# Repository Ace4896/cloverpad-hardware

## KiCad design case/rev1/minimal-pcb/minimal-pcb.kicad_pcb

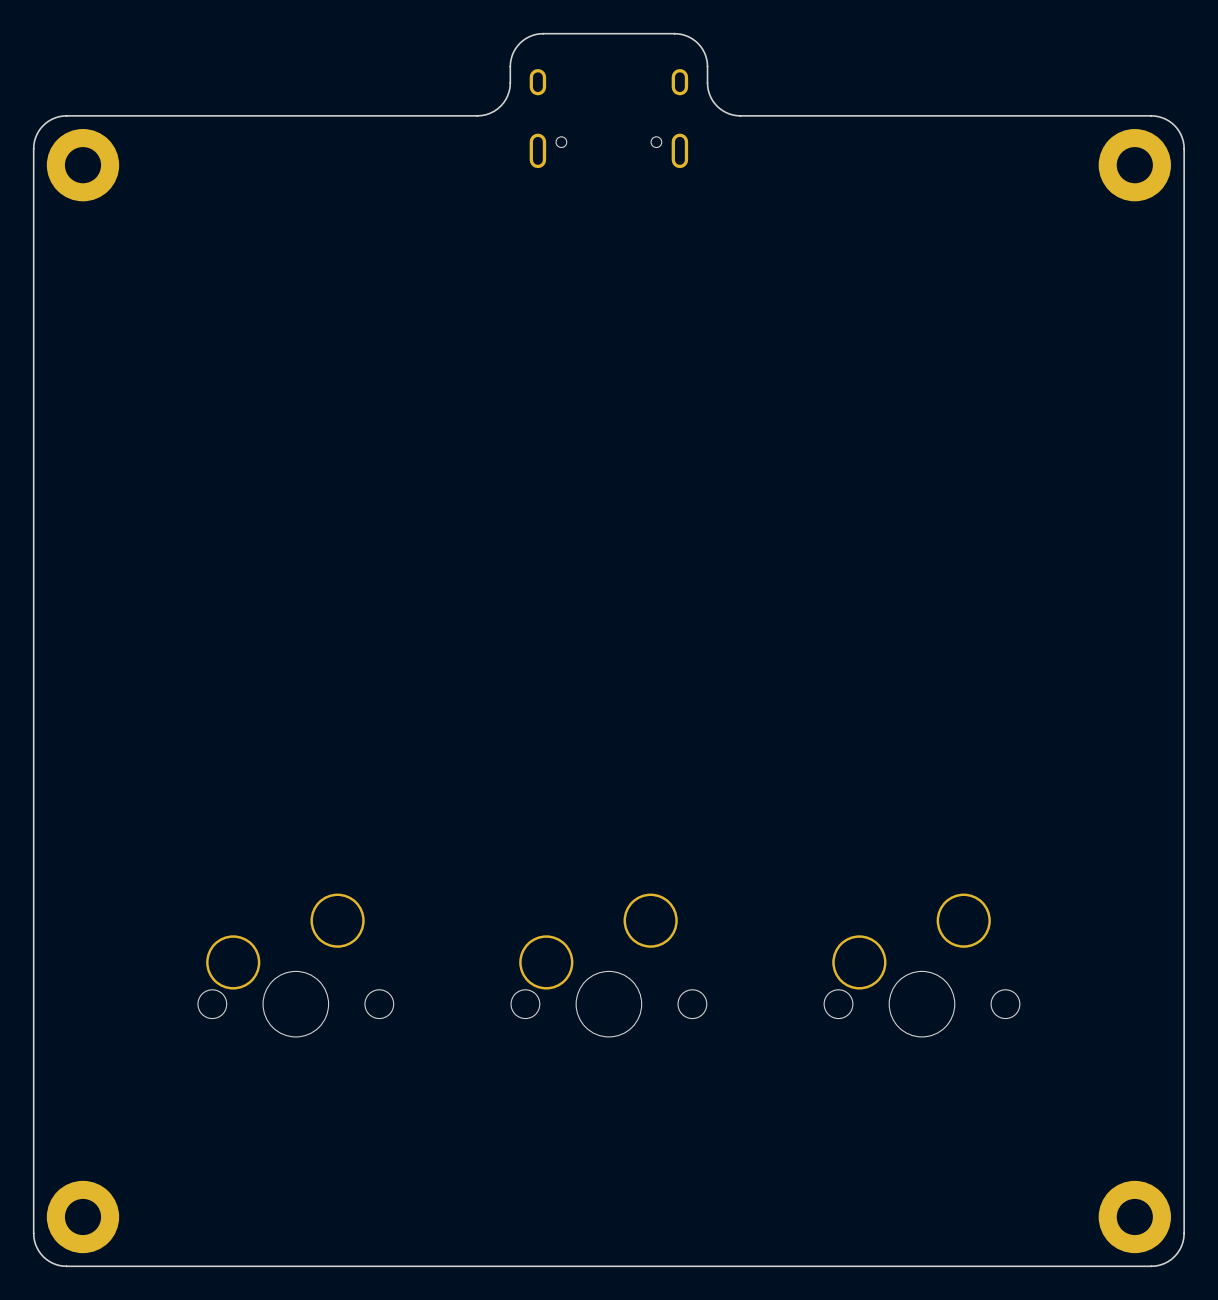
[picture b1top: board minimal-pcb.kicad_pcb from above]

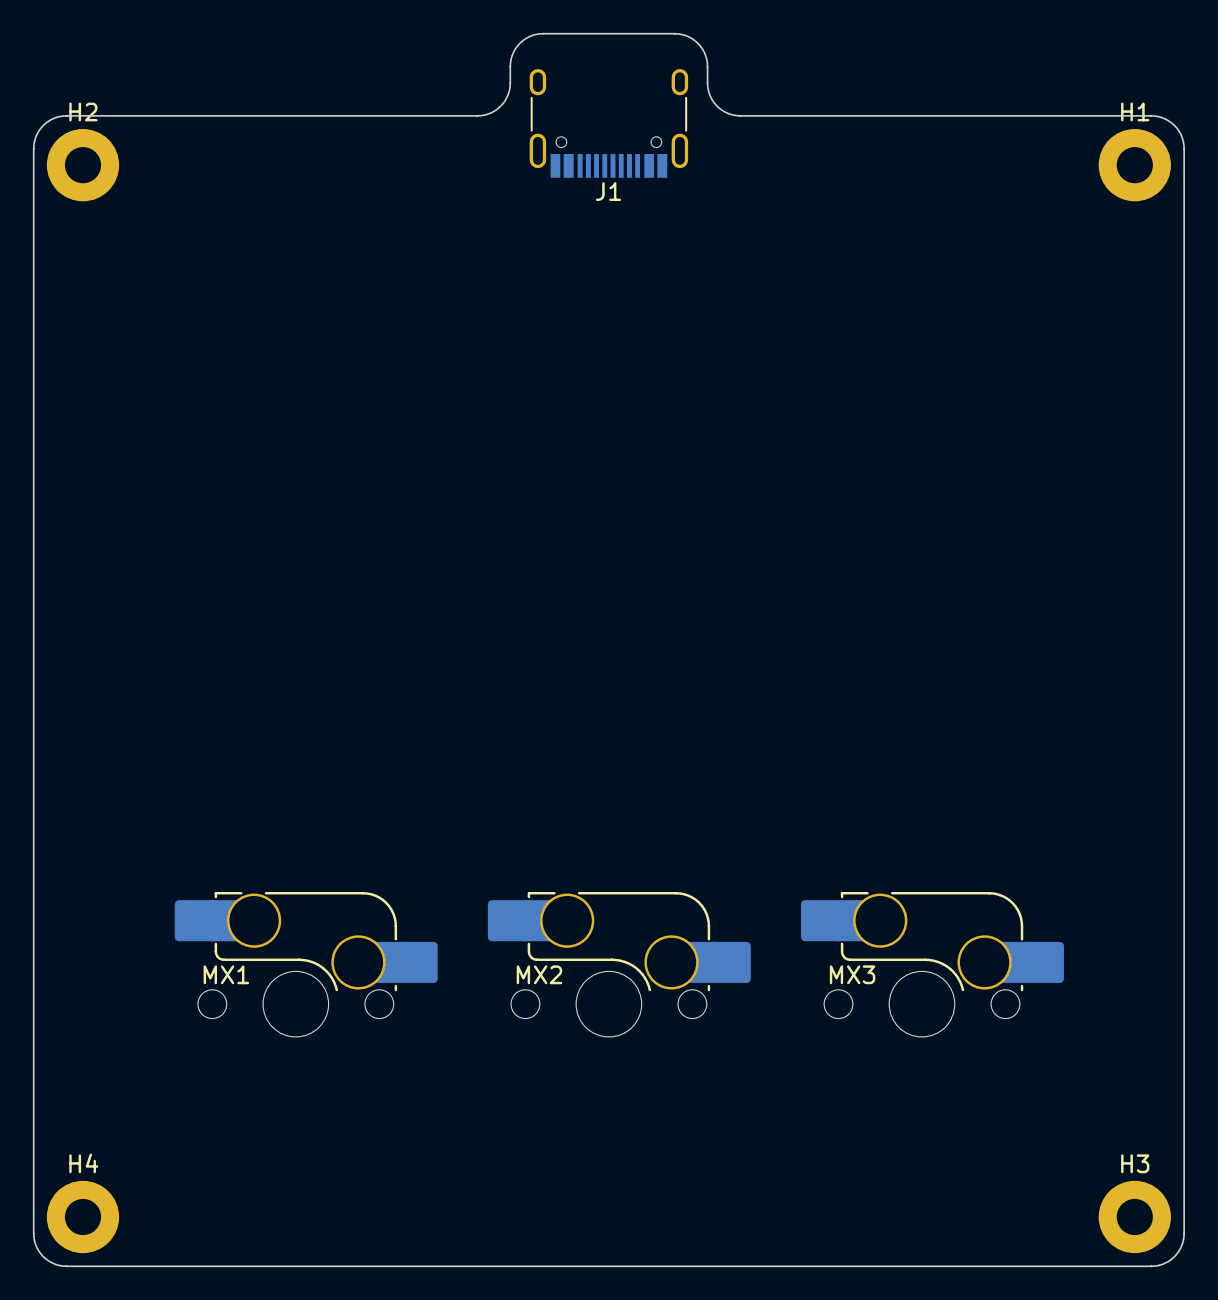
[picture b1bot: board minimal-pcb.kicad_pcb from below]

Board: 2 copper layers, 70.0 x 75.0 mm, 8 parts (8 on the bottom side), 2 nets, no tracks yet.

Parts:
H1, H2, H3, H4: Mounting Hole; MountingHole_2.2mm_M2_Pad
J1: USB_C_Receptacle_USB2.0; USB_C_Receptacle_HRO_TYPE-C-31-M-12
MX1, MX2, MX3: MX_SW_HS; SW_MX_HS_1u

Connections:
unnamed: J1.A1 (GND), J1.A12 (GND), J1.B1 (GND), J1.B12 (GND)
unnamed: J1.A4 (VBUS), J1.A9 (VBUS), J1.B4 (VBUS), J1.B9 (VBUS)

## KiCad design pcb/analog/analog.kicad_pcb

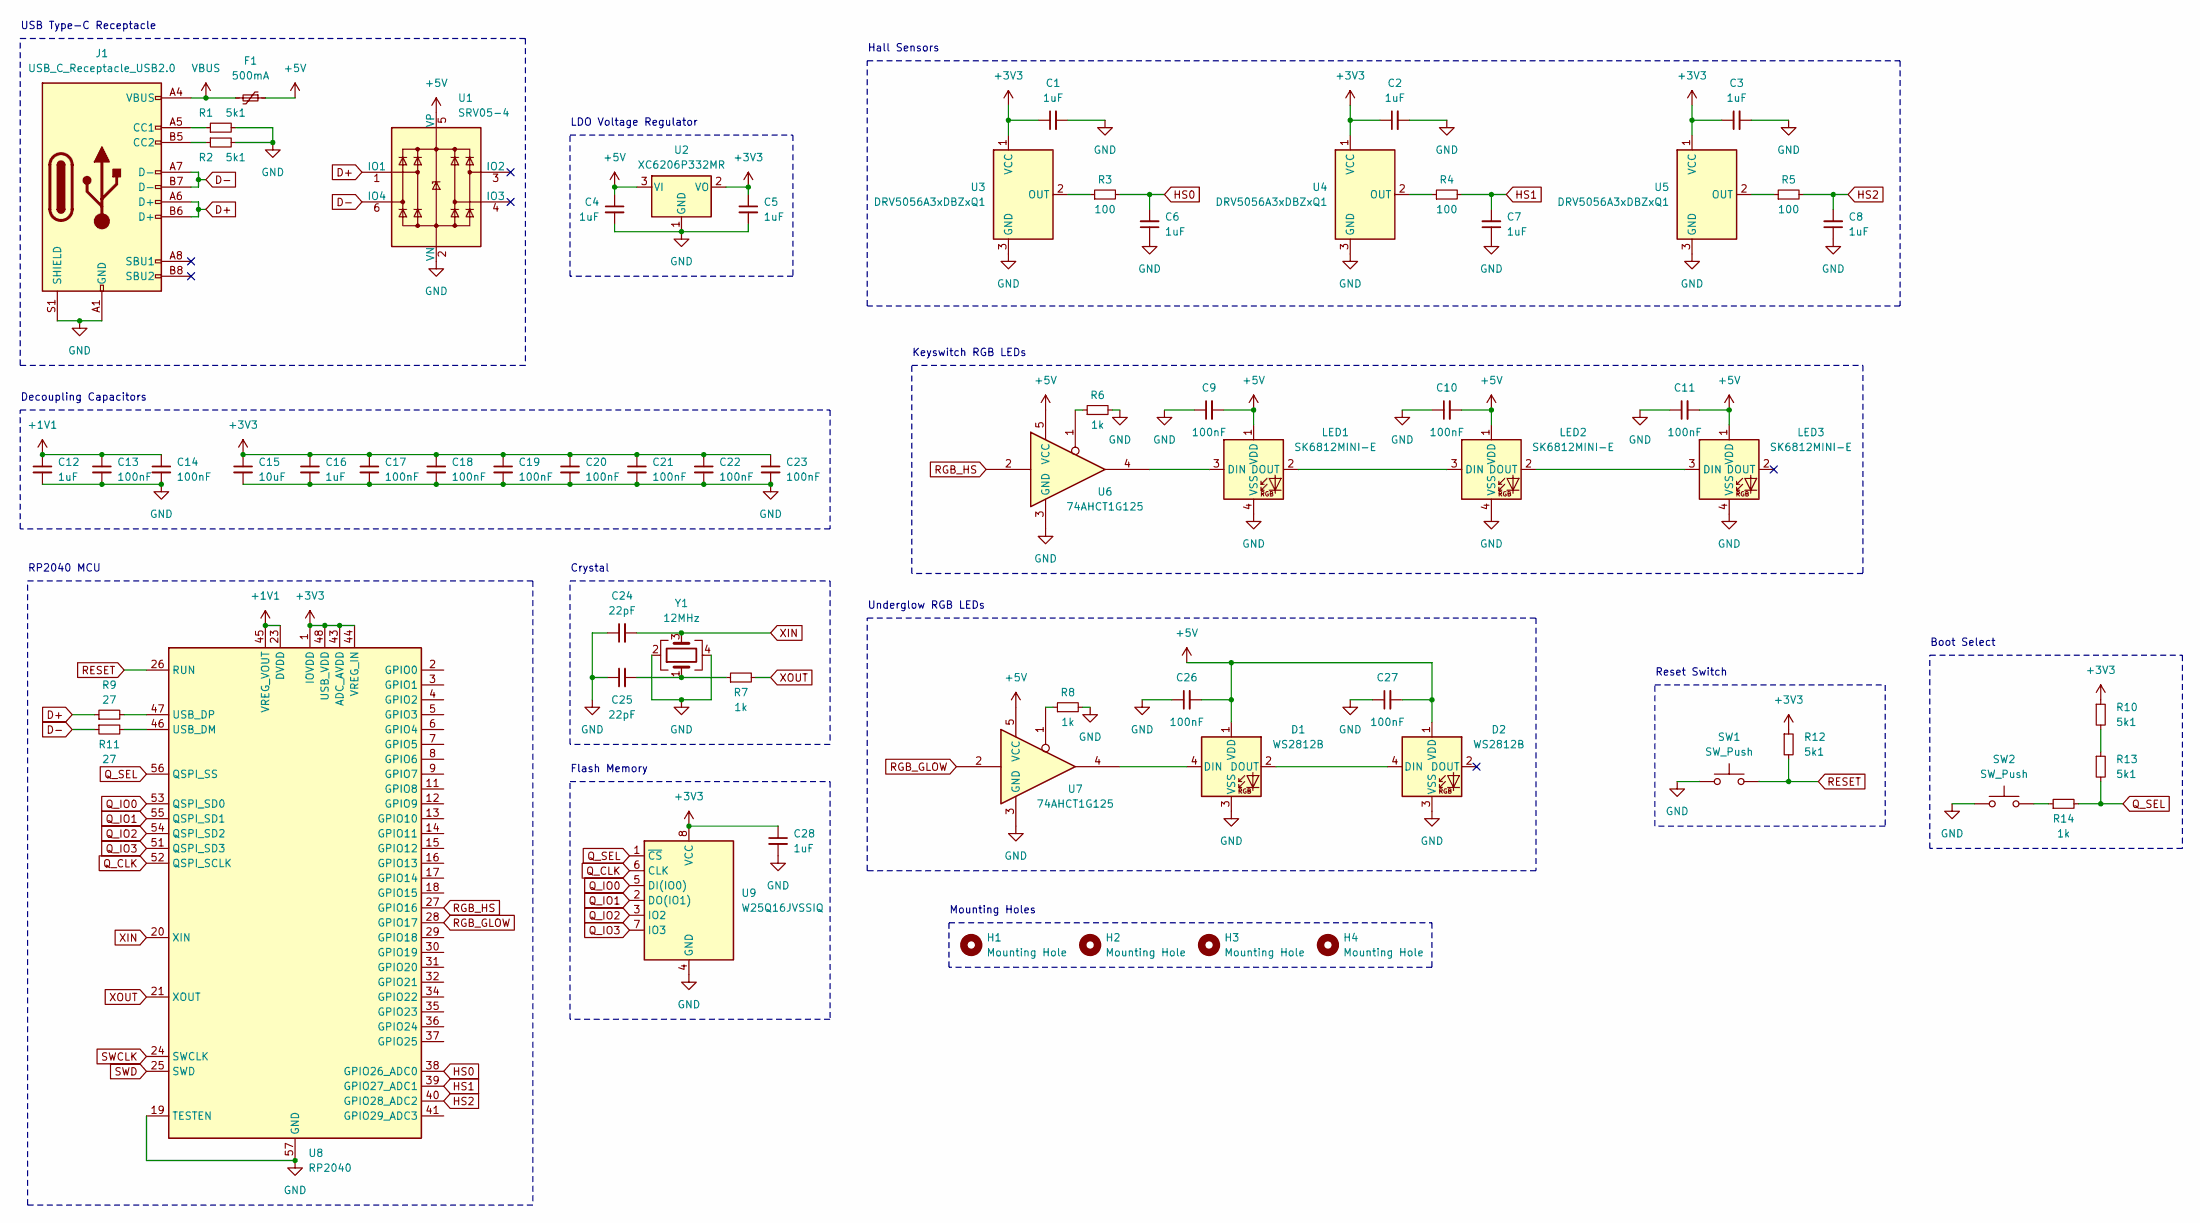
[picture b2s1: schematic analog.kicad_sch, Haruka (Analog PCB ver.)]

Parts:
C1, C2, C3, C4, C5, C6, C7, C8, C12, C16, C28: 1uF; C_0402_1005Metric; LCSC C52923
C9, C10, C11, C13, C14, C17, C18, C19, C20, C21, C22, C23, C26, C27: 100nF; C_0402_1005Metric; LCSC C1525
C15: 10uF; C_0603_1608Metric; LCSC C19702
C24, C25: 22pF; C_0402_1005Metric; LCSC C1555
D1, D2: WS2812B; LED_WS2812B_PLCC4_5.0x5.0mm_P3.2mm; LCSC C2761795
F1: 500mA; Fuse_1206_3216Metric; LCSC C170165
H1, H2, H3, H4: Mounting Hole; MountingHole_4mm
J1: USB_C_Receptacle_USB2.0; USB_C_Receptacle_HRO_TYPE-C-31-M-12; LCSC C165948
LED1, LED2, LED3: SK6812MINI-E; LED_MX_6028R; LCSC C5149201
R1, R2, R10, R12, R13: 5k1; R_0402_1005Metric; LCSC C25905
R3, R4, R5: 100; R_0402_1005Metric; LCSC C25076
R6, R7, R8, R14: 1k; R_0402_1005Metric; LCSC C11702
R9, R11: 27; R_0402_1005Metric; LCSC C25100
SW1, SW2: SW_Push; SW_SPST_TL3342; LCSC C318884
U1: SRV05-4; SOT-23-6-routable; LCSC C2836319
U2: XC6206P332MR; SOT-23-3; LCSC C5446
U3, U4, U5: DRV5056A3xDBZxQ1; KS-20-1U-DRV5056; LCSC C2152965
U6, U7: 74AHCT1G125; SOT-353_SC-70-5; LCSC C151417
U8: RP2040; QFN-56-1EP_7x7mm_P0.4mm_EP3.2x3.2mm; LCSC C2040
U9: W25Q16JVSSIQ; SOIC-8_5.23x5.23mm_P1.27mm; LCSC C131025
Y1: 12MHz; Crystal_SMD_3225-4Pin_3.2x2.5mm; LCSC C9002

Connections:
+1V1: C12.1, C13.1, C14.1, U8.23 (DVDD), U8.45 (VREG_VOUT), U8.50 (DVDD)
+3V3: C1.1, C2.1, C3.1, C5.1, C15.1, C16.1, C17.1, C18.1, C19.1, C20.1, C21.1, C22.1, C23.1, C28.1, R10.1, R12.1, U2.2 (VO), U3.1 (VCC), U4.1 (VCC), U5.1 (VCC), U8.1 (IOVDD), U8.10 (IOVDD), U8.22 (IOVDD), U8.33 (IOVDD), U8.42 (IOVDD), U8.43 (ADC_AVDD), U8.44 (VREG_IN), U8.48 (USB_VDD), U8.49 (IOVDD), U9.8 (VCC)
+5V: C4.1, C9.2, C10.2, C11.2, C26.2, C27.2, D1.1 (VDD), D2.1 (VDD), F1.1, LED1.1 (VDD), LED2.1 (VDD), LED3.1 (VDD), U1.5 (VP), U2.3 (VI), U6.5 (VCC), U7.5 (VCC)
D+: J1.A6 (D+), J1.B6 (D+), R9.1, U1.1 (IO1)
D-: J1.A7 (D-), J1.B7 (D-), R11.1, U1.6 (IO4)
GND: C1.2, C2.2, C3.2, C4.2, C5.2, C6.1, C7.1, C8.1, C9.1, C10.1, C11.1, C12.2, C13.2, C14.2, C15.2, C16.2, C17.2, C18.2, C19.2, C20.2, C21.2, C22.2, C23.2, C24.1, C25.1, C26.1, C27.1, C28.2, D1.3 (VSS), D2.3 (VSS), J1.A1 (GND), J1.A12 (GND), J1.B1 (GND), J1.B12 (GND), J1.S1 (SHIELD), LED1.4 (VSS), LED2.4 (VSS), LED3.4 (VSS), R1.2, R2.2, R6.2, R8.2, SW1.1, SW2.1, U1.2 (VN), U2.1 (GND), U3.3 (GND), U4.3 (GND), U5.3 (GND), U6.3 (GND), U7.3 (GND), U8.19 (TESTEN), U8.57 (GND), U9.4 (GND), Y1.2, Y1.4
HS0: C6.2, R3.2, U8.38 (GPIO26_ADC0)
HS1: C7.2, R4.2, U8.39 (GPIO27_ADC1)
HS2: C8.2, R5.2, U8.40 (GPIO28_ADC2)
unnamed: C25.2, R7.1, Y1.1
unnamed: D1.4 (DIN), U7.4
unnamed: D1.2 (DOUT), D2.4 (DIN)
unnamed: J1.A5 (CC1), R1.1
unnamed: J1.B5 (CC2), R2.1
unnamed: LED1.3 (DIN), U6.4
unnamed: LED1.2 (DOUT), LED2.3 (DIN)
unnamed: LED2.2 (DOUT), LED3.3 (DIN)
unnamed: R6.1, U6.1
unnamed: R8.1, U7.1
unnamed: R10.2, R13.1
unnamed: R14.1, SW2.2
unnamed: R3.1, U3.2 (OUT)
unnamed: R4.1, U4.2 (OUT)
unnamed: R5.1, U5.2 (OUT)
unnamed: R11.2, U8.46 (USB_DM)
unnamed: R9.2, U8.47 (USB_DP)
Q_CLK: U8.52 (QSPI_SCLK), U9.6 (CLK)
Q_IO0: U8.53 (QSPI_SD0), U9.5 (DI(IO0))
Q_IO1: U8.55 (QSPI_SD1), U9.2 (DO(IO1))
Q_IO2: U8.54 (QSPI_SD2), U9.3 (IO2)
Q_IO3: U8.51 (QSPI_SD3), U9.7 (IO3)
Q_SEL: R13.2, R14.2, U8.56 (QSPI_SS), U9.1 (~CS)
RESET: R12.2, SW1.2, U8.26 (RUN)
RGB_GLOW: U7.2, U8.28 (GPIO17)
RGB_HS: U6.2, U8.27 (GPIO16)
SWCLK: U8.24 (SWCLK)
SWD: U8.25 (SWD)
VBUS: F1.2, J1.A4 (VBUS), J1.A9 (VBUS), J1.B4 (VBUS), J1.B9 (VBUS)
XIN: C24.2, U8.20 (XIN), Y1.3
XOUT: R7.2, U8.21 (XOUT)

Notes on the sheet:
Reset Switch
Keyswitch RGB LEDs
USB Type-C Receptacle
Mounting Holes
Decoupling Capacitors
LDO Voltage Regulator
Hall Sensors
Underglow RGB LEDs
RP2040 MCU
Flash Memory
Boot Select
Crystal

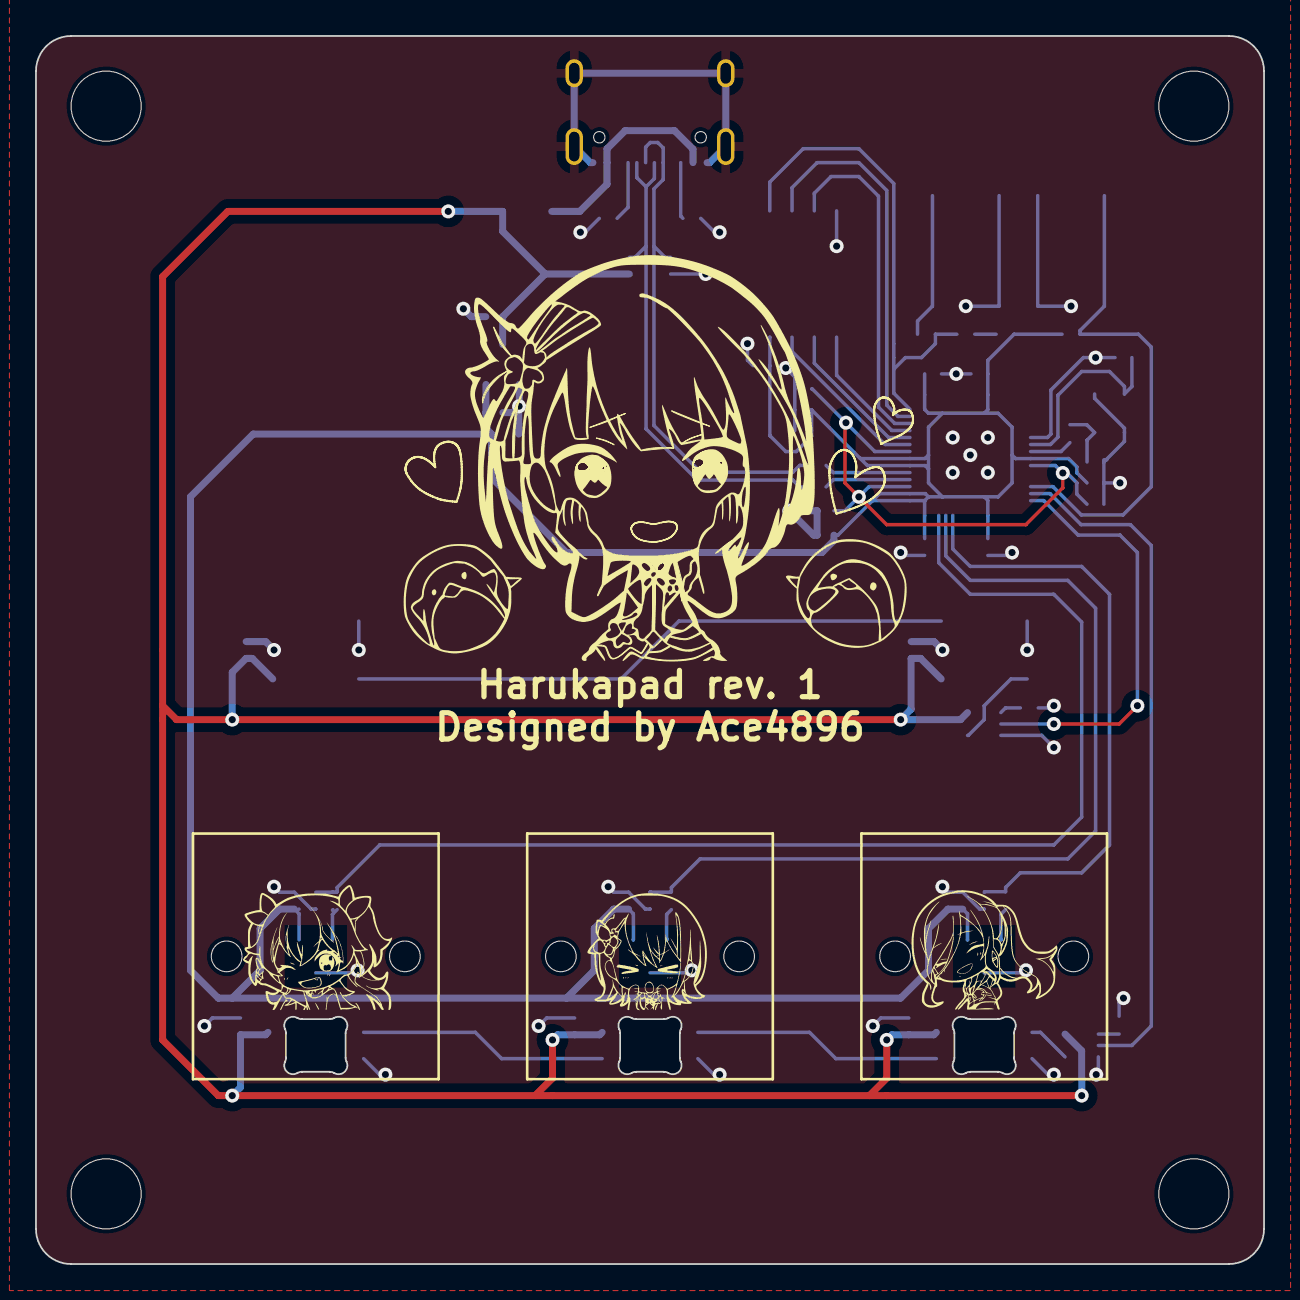
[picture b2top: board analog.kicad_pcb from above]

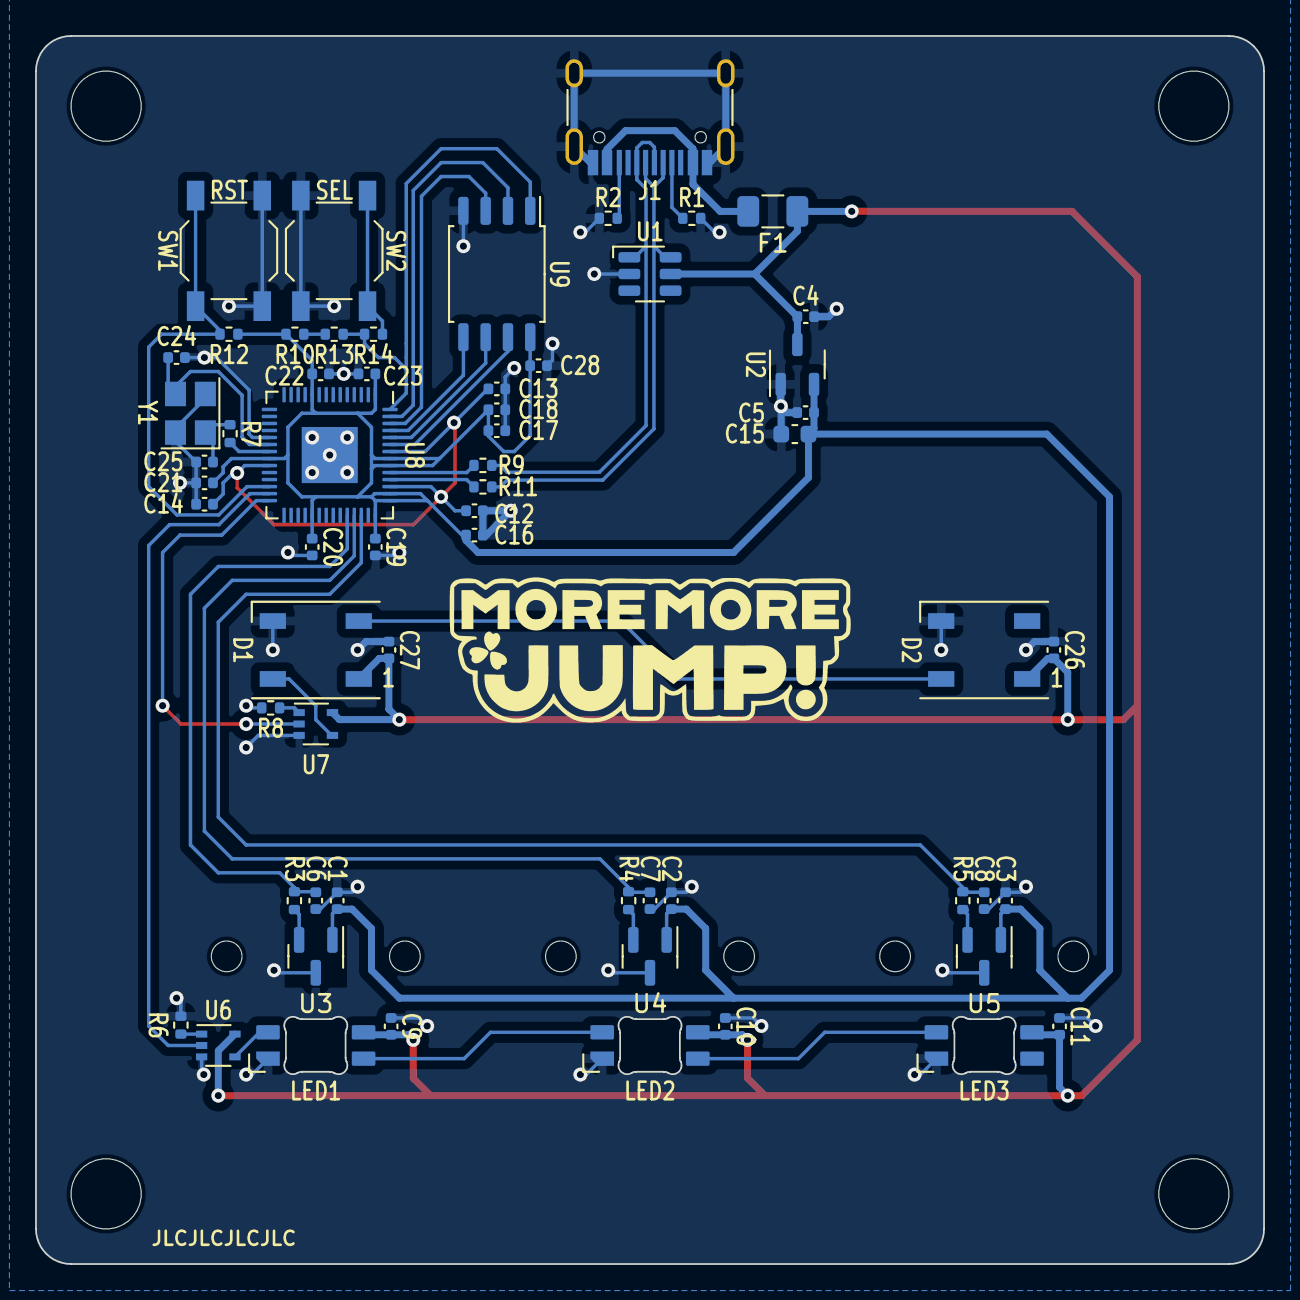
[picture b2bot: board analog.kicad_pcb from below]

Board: 2 copper layers, 70.0 x 70.0 mm, 65 parts (61 on the bottom side), 38 nets.
